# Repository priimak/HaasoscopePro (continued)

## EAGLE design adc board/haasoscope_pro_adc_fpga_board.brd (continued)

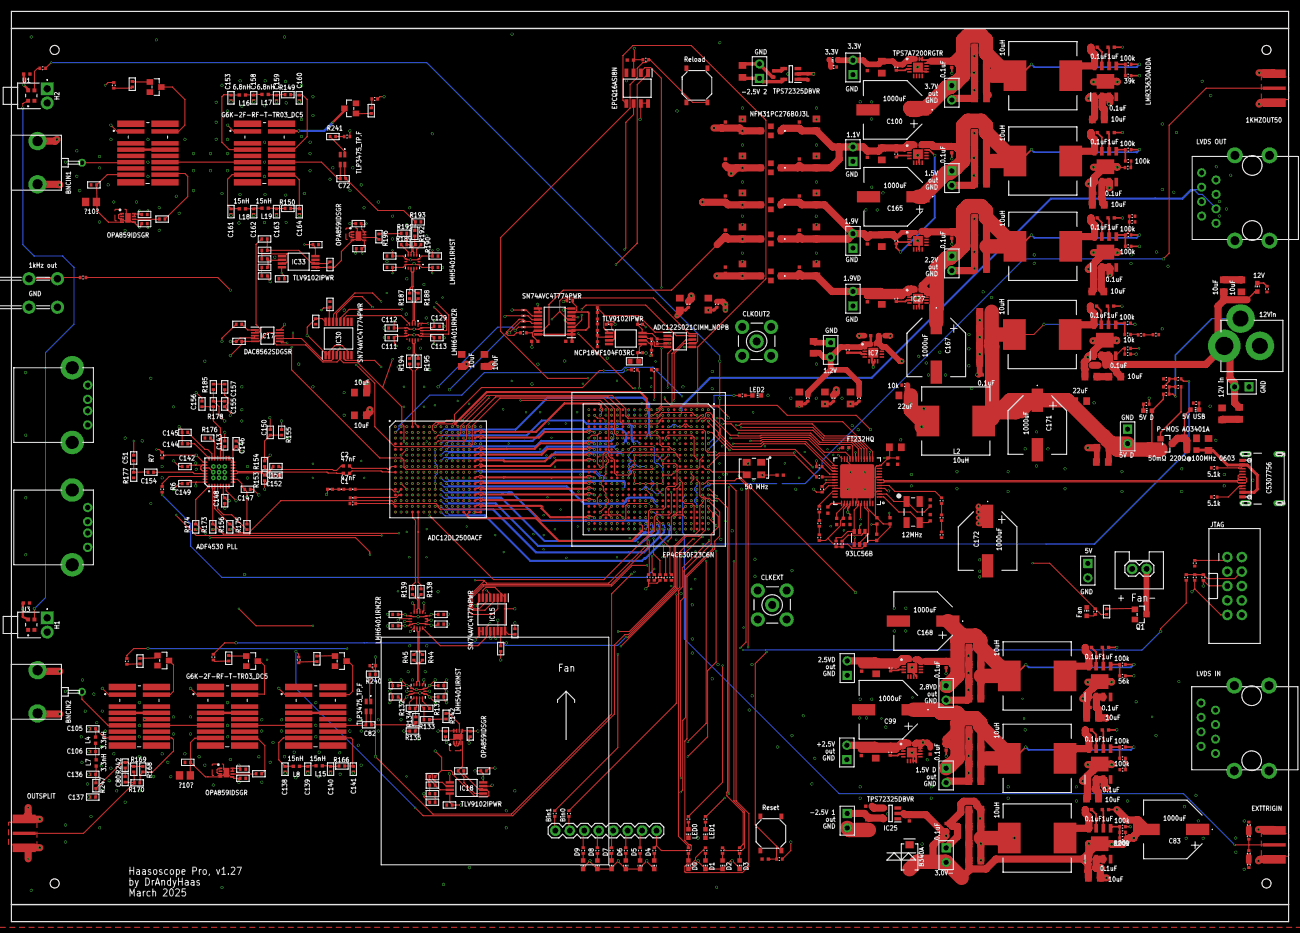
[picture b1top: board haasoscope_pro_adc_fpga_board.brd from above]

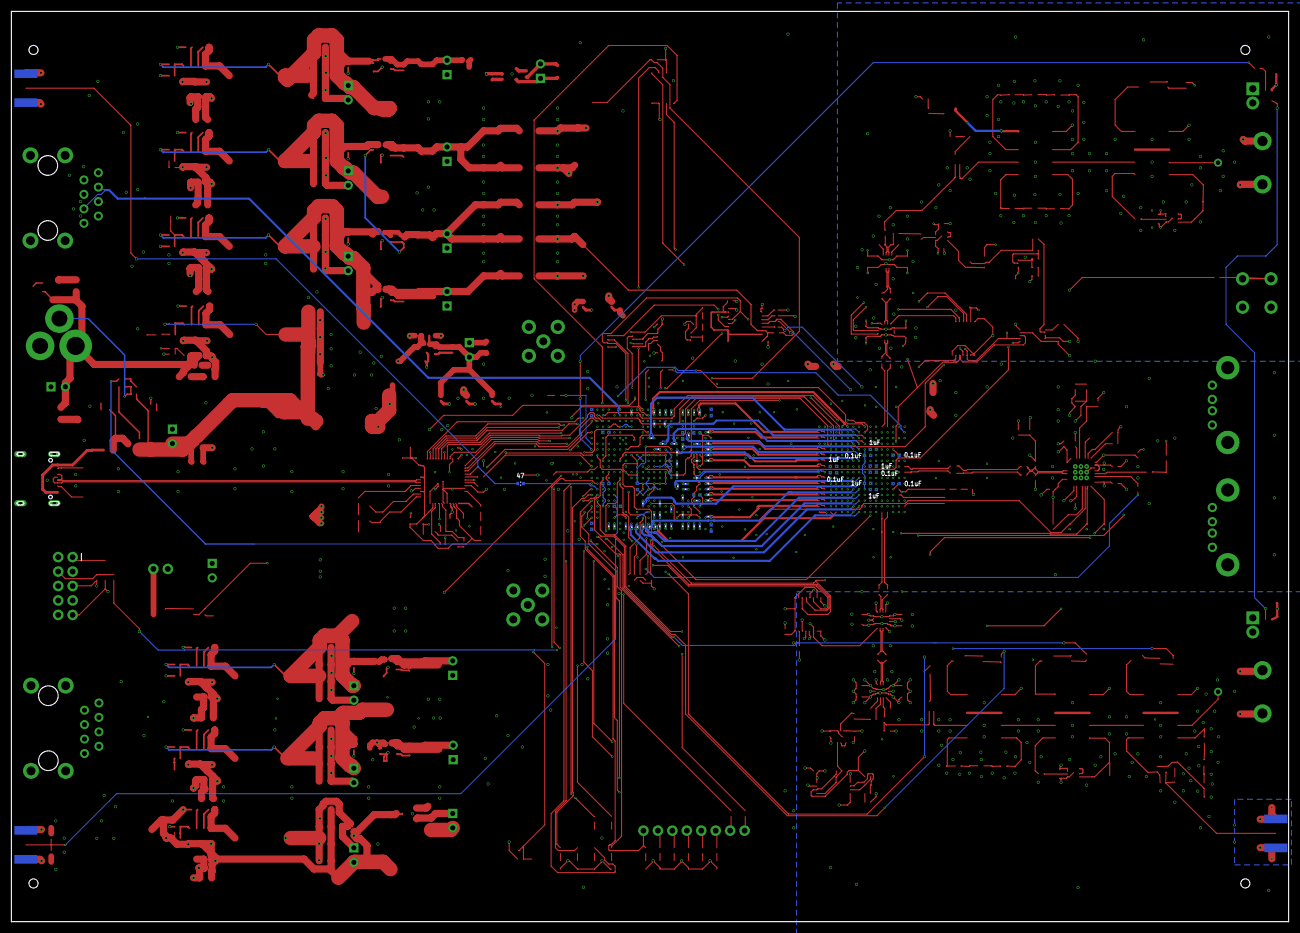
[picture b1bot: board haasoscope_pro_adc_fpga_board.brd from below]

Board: 10 copper layers, 224.5 x 160.0 mm, 632 parts (82 on the bottom side), 494 nets.

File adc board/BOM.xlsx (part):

0 | 0402_RES | R128,R129 | C17168 0402WGF0000TCE 62.5mW Thick Film Resistors 50V ±800ppm/℃ ±1% 0Ω 0402 Chi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
0 | RES-0402 | R15,R18,R81,R87,R88,R89,R90 | C17168 0402WGF0000TCE 62.5mW Thick Film Resistors 50V ±800ppm/℃ ±1% 0Ω 0402 Chi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
0 | R0402 | R142,R149,R150,R155,R166,R196,R245,R247 | C17168 0402WGF0000TCE 62.5mW Thick Film Resistors 50V ±800ppm/℃ ±1% 0Ω 0402 Chi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
22.6 | R0402 | R134,R192 | C172030 WR04X22R6FTL 62.5mW Thick Film Resistors 50V ±100ppm/℃ ±1% 22.6Ω 0402 C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
39 | R0402 | R44,R45,R138,R139 | C185420 RC0402FR-0739RL 62.5mW Thick Film Resistors 50V ±100ppm/℃ ±1% 39Ω 0402 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
39 | RES-0402 | R184 | C185420 RC0402FR-0739RL 62.5mW Thick Film Resistors 50V ±100ppm/℃ ±1% 39Ω 0402 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
39 | R0402 | R187,R188,R194,R195 | C185420 RC0402FR-0739RL 62.5mW Thick Film Resistors 50V ±100ppm/℃ ±1% 39Ω 0402 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
47 | R0402 | R43 | C25118 0402WGF470JTCE 62.5mW Thick Film Resistors 50V ±1% ±200ppm/℃ 47Ω 0402 Ch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
47 | RES-0402 | R31 | C25118 0402WGF470JTCE 62.5mW Thick Film Resistors 50V ±1% ±200ppm/℃ 47Ω 0402 Ch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
47 | R0402 | R242 | C25118 0402WGF470JTCE 62.5mW Thick Film Resistors 50V ±1% ±200ppm/℃ 47Ω 0402 Ch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
47 | RES-0402 | R160 | C25118 0402WGF470JTCE 62.5mW Thick Film Resistors 50V ±1% ±200ppm/℃ 47Ω 0402 Ch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
47 | RES-0402 | R211 | C25118 0402WGF470JTCE 62.5mW Thick Film Resistors 50V ±1% ±200ppm/℃ 47Ω 0402 Ch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
47 | R0402 | R153,R154,R159 | C25118 0402WGF470JTCE 62.5mW Thick Film Resistors 50V ±1% ±200ppm/℃ 47Ω 0402 Ch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
47 | RES-0402 | R136 | C25118 0402WGF470JTCE 62.5mW Thick Film Resistors 50V ±1% ±200ppm/℃ 47Ω 0402 Ch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
47 | RES-0402 | R210 | C25118 0402WGF470JTCE 62.5mW Thick Film Resistors 50V ±1% ±200ppm/℃ 47Ω 0402 Ch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
47 | R0402 | R168,R169,R170,R177 | C25118 0402WGF470JTCE 62.5mW Thick Film Resistors 50V ±1% ±200ppm/℃ 47Ω 0402 Ch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
66.5 | R0402 | R133,R191 | C368442 WR04X66R5FTL 62.5mW Thick Film Resistors 50V ±100ppm/℃ ±1% 66.5Ω 0402 C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
100 | R0201 | R1,R2,R3,R4 | C270366 0201WMF1000TEE 50mW Thick Film Resistors 25V ±1% ±200ppm/℃ 100Ω 0201 Ch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
100 | R0201 | R17,R19,R20,R21,R23,R24,R25,R26,R39,R54,R55,R56,R57,R58,R59,R60,R61,R62,R63,R64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 | C270366 0201WMF1000TEE 50mW Thick Film Resistors 25V ±1% ±200ppm/℃ 100Ω 0201 Ch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
120 | R0402 | R240,R241 | C25079 0402WGF1200TCE 62.5mW Thick Film Resistors 50V ±100ppm/℃ ±1% 120Ω 0402 C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
127 | R0402 | R131,R132,R189,R190 | C1509602 ARG02BTC1270 62.5mW Thin Film Resistor 50V ±25ppm/℃ ±0.1% 127Ω 0402 Ch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
220 | R0402 | R135,R193 | C25091 0402WGF2200TCE 62.5mW Thick Film Resistors 50V ±100ppm/℃ ±1% 220Ω 0402 C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
357 | RES-0402 | R50 | C423184 0402WGF3570TCE 62.5mW Thick Film Resistors 50V ±100ppm/℃ ±1% 357Ω 0402 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
357 | R0402 | R185 | C423184 0402WGF3570TCE 62.5mW Thick Film Resistors 50V ±100ppm/℃ ±1% 357Ω 0402 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
0.1uF | C0402 | C78,C84,C85,C86,C87,C88,C89,C90,C91,C92,C93,C94,C95,C96,C97,C98,C107,C108,C109,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 | C1525 CL05B104KO5NNNC 16V 100nF X7R ±10% 0402 Multilayer Ceramic Capacitors MLC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
0.1uF | RESC0402_N | C3,C4,C7,C9,C17,C19,C27,C29,C37,C39 | C1525 CL05B104KO5NNNC 16V 100nF X7R ±10% 0402 Multilayer Ceramic Capacitors MLC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
0.1uF | RESC0402_N | C12,C20,C23,C31,C33,C61,C62,C63,C64,C65,C66,C67,C68,C69,C70,C71 | C1525 CL05B104KO5NNNC 16V 100nF X7R ±10% 0402 Multilayer Ceramic Capacitors MLC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
0.1uF | RESC0402_N | C58,C59,C60,C73,C74 | C1525 CL05B104KO5NNNC 16V 100nF X7R ±10% 0402 Multilayer Ceramic Capacitors MLC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
0.1uF | C0402 | C129,C130,C131,C132,C133,C134,C135,C142,C143,C144,C145,C146,C147,C148,C149,C150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 | C1525 CL05B104KO5NNNC 16V 100nF X7R ±10% 0402 Multilayer Ceramic Capacitors MLC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
0.1uF | C0402 | C75 | C1525 CL05B104KO5NNNC 16V 100nF X7R ±10% 0402 Multilayer Ceramic Capacitors MLC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
0.1uF | RESC0402_N | C53,C54 | C1525 CL05B104KO5NNNC 16V 100nF X7R ±10% 0402 Multilayer Ceramic Capacitors MLC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
0.1uF | RESC0402_N | C114,C115,C116,C117,C119,C121,C122,C123,C124,C125 | C1525 CL05B104KO5NNNC 16V 100nF X7R ±10% 0402 Multilayer Ceramic Capacitors MLC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
0.1uF | 0402_CAP | C50 | C1525 CL05B104KO5NNNC 16V 100nF X7R ±10% 0402 Multilayer Ceramic Capacitors MLC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
0.1uF | 0402_CAP | C44 | C1525 CL05B104KO5NNNC 16V 100nF X7R ±10% 0402 Multilayer Ceramic Capacitors MLC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
0.1uF | RESC0402_N | C47,C49 | C1525 CL05B104KO5NNNC 16V 100nF X7R ±10% 0402 Multilayer Ceramic Capacitors MLC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
0.1uF | C0402 | C55,C56 | C1525 CL05B104KO5NNNC 16V 100nF X7R ±10% 0402 Multilayer Ceramic Capacitors MLC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
0.1uF | RESC0402_N | C77 | C1525 CL05B104KO5NNNC 16V 100nF X7R ±10% 0402 Multilayer Ceramic Capacitors MLC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
0.1uF | C0402 | C51 | C1525 CL05B104KO5NNNC 16V 100nF X7R ±10% 0402 Multilayer Ceramic Capacitors MLC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
0.1uF | RESC0402_N | C245,C247,C249,C250,C252,C254,C256,C258,C259,C260,C262,C263,C264,C266,C267,C268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 | C307331 CL05B104KB54PNC 50V 100nF X7R ±10% 0402 Multilayer Ceramic Capacitors M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
1.0pF | C0402 | C101,C103,C105,C136 | C1550 0402CG1R0C500NT 50V 1pF C0G 0402 Multilayer Ceramic Capacitors MLCC - SMD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
1.5pF | C0402 | C102,C106 | C1552 0402CG1R5C500NT 50V 1.5pF C0G 0402 Multilayer Ceramic Capacitors MLCC - S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
100k | RES-0402 | R137,R163,R209,R221,R223,R224,R225,R226,R227,R229,R230,R231,R232,R233 | C25741 0402WGF1003TCE 62.5mW Thick Film Resistors 50V ±100ppm/℃ ±1% 100kΩ 0402 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
10k | 0402_RES | R186,R198 | C25744 0402WGF1002TCE 62.5mW Thick Film Resistors 50V ±100ppm/℃ ±1% 10kΩ 0402 C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
10k | RES-0402 | R151 | C25744 0402WGF1002TCE 62.5mW Thick Film Resistors 50V ±100ppm/℃ ±1% 10kΩ 0402 C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
10k | R0402 | R173,R174,R175 | C25744 0402WGF1002TCE 62.5mW Thick Film Resistors 50V ±100ppm/℃ ±1% 10kΩ 0402 C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
10k | 0402_RES | R125,R127,R130 | C25744 0402WGF1002TCE 62.5mW Thick Film Resistors 50V ±100ppm/℃ ±1% 10kΩ 0402 C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
10k | RES-0402 | R212,R213,R214,R215,R216,R219,R220,R234,R237,R239 | C25744 0402WGF1002TCE 62.5mW Thick Film Resistors 50V ±100ppm/℃ ±1% 10kΩ 0402 C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
10k | RES-0402 | R161 | C25744 0402WGF1002TCE 62.5mW Thick Film Resistors 50V ±100ppm/℃ ±1% 10kΩ 0402 C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
10k | R0402 | R156 | C25744 0402WGF1002TCE 62.5mW Thick Film Resistors 50V ±100ppm/℃ ±1% 10kΩ 0402 C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
10k | RES-0402 | R5,R27,R38,R78,R79,R80,R82,R83,R84,R85,R86,R91,R92,R121,R123 | C25744 0402WGF1002TCE 62.5mW Thick Film Resistors 50V ±100ppm/℃ ±1% 10kΩ 0402 C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
10uF | RESC0805_N | C6,C8,C10,C13,C16,C18,C21,C24,C26,C28,C34,C36,C38,C40,C41,C42,C43,C46,C48,C52,C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 | C15850 CL21A106KAYNNNE 25V 10uF X5R ±10% 0805 Multilayer Ceramic Capacitors MLC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
10uH | CDRH125 | L1,L9,L10,L11,L12,L13,L14 | C339970 YDRH105R-100M 4.45A 10uH ±20% SMD,10.1x10.1mm Power Inductors ROHS Exte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
11pF | C0402 | C139,C162 | C161525 GRM1555C1H110JA01D 50V 11pF C0G ±5% 0402 Multilayer Ceramic Capacitors 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
12MHz | CRYSTAL-SMD-5X3 | Y3 | C2901628 SX5B12.000F1620F30 12MHz SMD crystal oscillator 16pF ±20ppm ±30ppm SMD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
15nH | RESC0402_N | L8,L15,L18,L19 | C27143 SDCL1005C15NJTDF 300mA 15nH ±5% 500mΩ 0402 Inductors (SMD) ROHS Extended
16pF | RESC0402_N | C127,C128 | C77590 CC0402JRNPO9BN160 50V 16pF NP0 ±5% 0402 Multilayer Ceramic Capacitors ML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
16pF | C0402 | C80 | C77590 CC0402JRNPO9BN160 50V 16pF NP0 ±5% 0402 Multilayer Ceramic Capacitors ML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
1k | RES-0402 | R179 | C11702 0402WGF1001TCE 62.5mW Thick Film Resistors 50V ±100ppm/℃ ±1% 1kΩ 0402 Ch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
1k | R0402 | R180,R181,R197,R199,R200,R201 | C11702 0402WGF1001TCE 62.5mW Thick Film Resistors 50V ±100ppm/℃ ±1% 1kΩ 0402 Ch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
1k | RES-0402 | R236,R238,R243,R244 | C11702 0402WGF1001TCE 62.5mW Thick Film Resistors 50V ±100ppm/℃ ±1% 1kΩ 0402 Ch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
1k | 0402_RES | R122,R124,R126 | C11702 0402WGF1001TCE 62.5mW Thick Film Resistors 50V ±100ppm/℃ ±1% 1kΩ 0402 Ch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
1k | 0402_RES | R202,R203 | C11702 0402WGF1001TCE 62.5mW Thick Film Resistors 50V ±100ppm/℃ ±1% 1kΩ 0402 Ch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
1k | R0402 | R162,R164,R171,R172,R178 | C11702 0402WGF1001TCE 62.5mW Thick Film Resistors 50V ±100ppm/℃ ±1% 1kΩ 0402 Ch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
1k | RES-0402 | R206 | C11702 0402WGF1001TCE 62.5mW Thick Film Resistors 50V ±100ppm/℃ ±1% 1kΩ 0402 Ch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
1k | R0402 | R208 | C11702 0402WGF1001TCE 62.5mW Thick Film Resistors 50V ±100ppm/℃ ±1% 1kΩ 0402 Ch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
1k | R0402 | R140,R141,R143,R144,R145,R146,R147 | C11702 0402WGF1001TCE 62.5mW Thick Film Resistors 50V ±100ppm/℃ ±1% 1kΩ 0402 Ch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

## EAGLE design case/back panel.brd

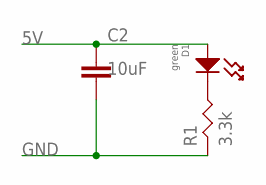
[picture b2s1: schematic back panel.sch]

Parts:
C2: 10uF; RESC0805_N
D1: green; LED0805
R1: 3.3k; RES-0402

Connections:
5V: C2.1, D1.ANODE
GND: C2.2, R1.P$1
unnamed: D1.CATHODE, R1.P$2

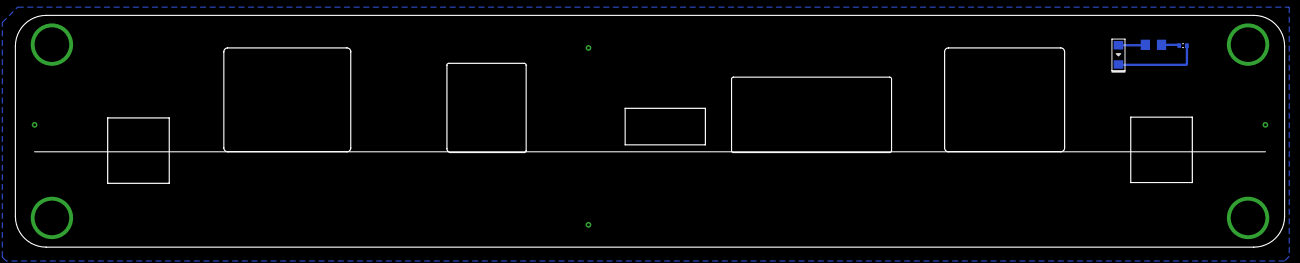
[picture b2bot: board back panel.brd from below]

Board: 2 copper layers, 165.0 x 30.1 mm, 5 parts (3 on the bottom side), 3 nets.

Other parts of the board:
U$1: CE_5MM
U$2: FCC_6.1X16MM

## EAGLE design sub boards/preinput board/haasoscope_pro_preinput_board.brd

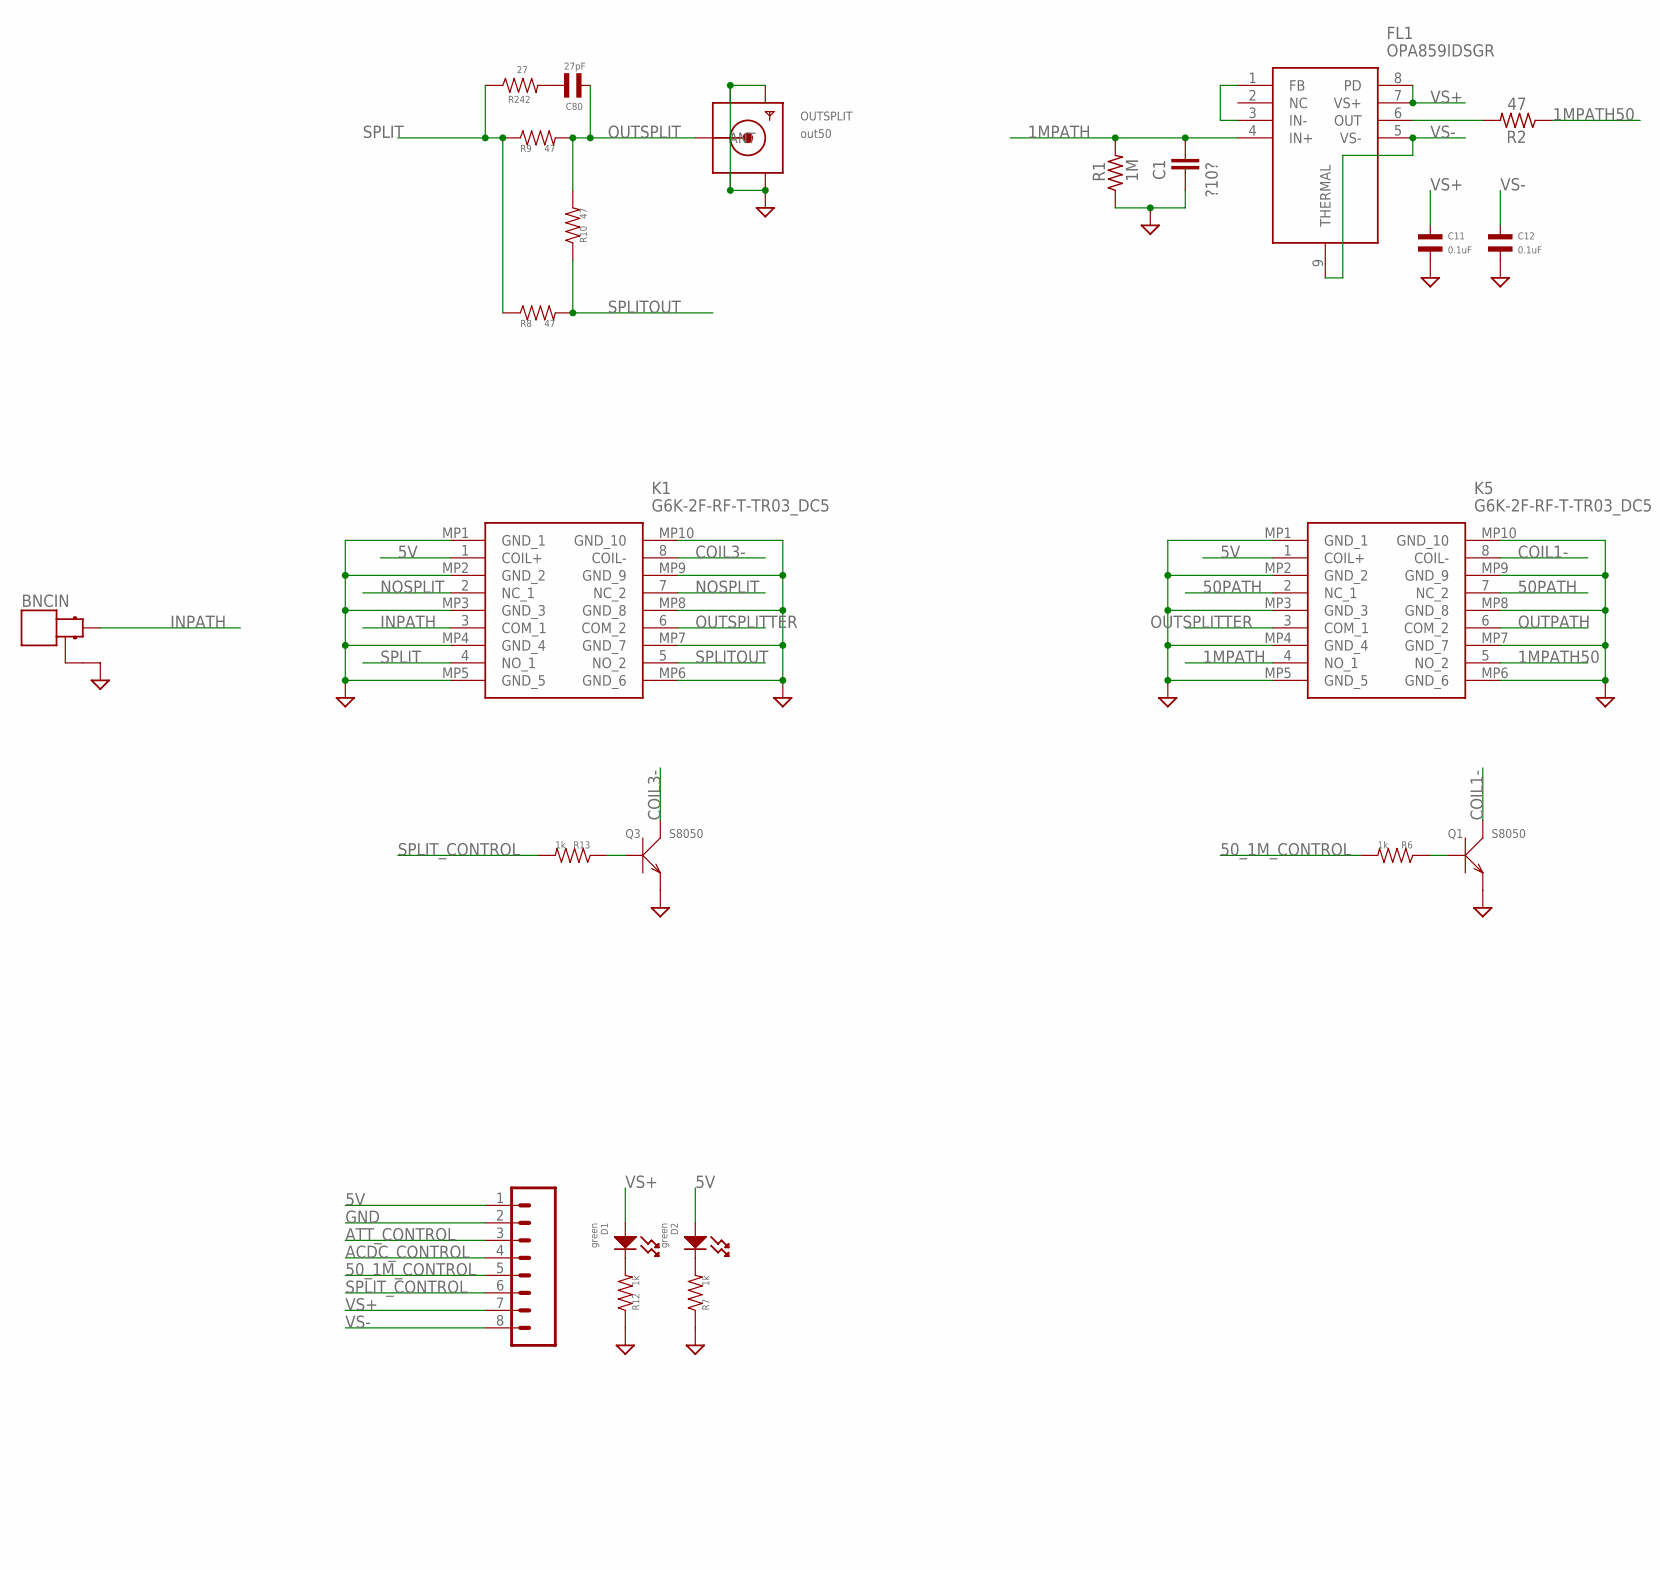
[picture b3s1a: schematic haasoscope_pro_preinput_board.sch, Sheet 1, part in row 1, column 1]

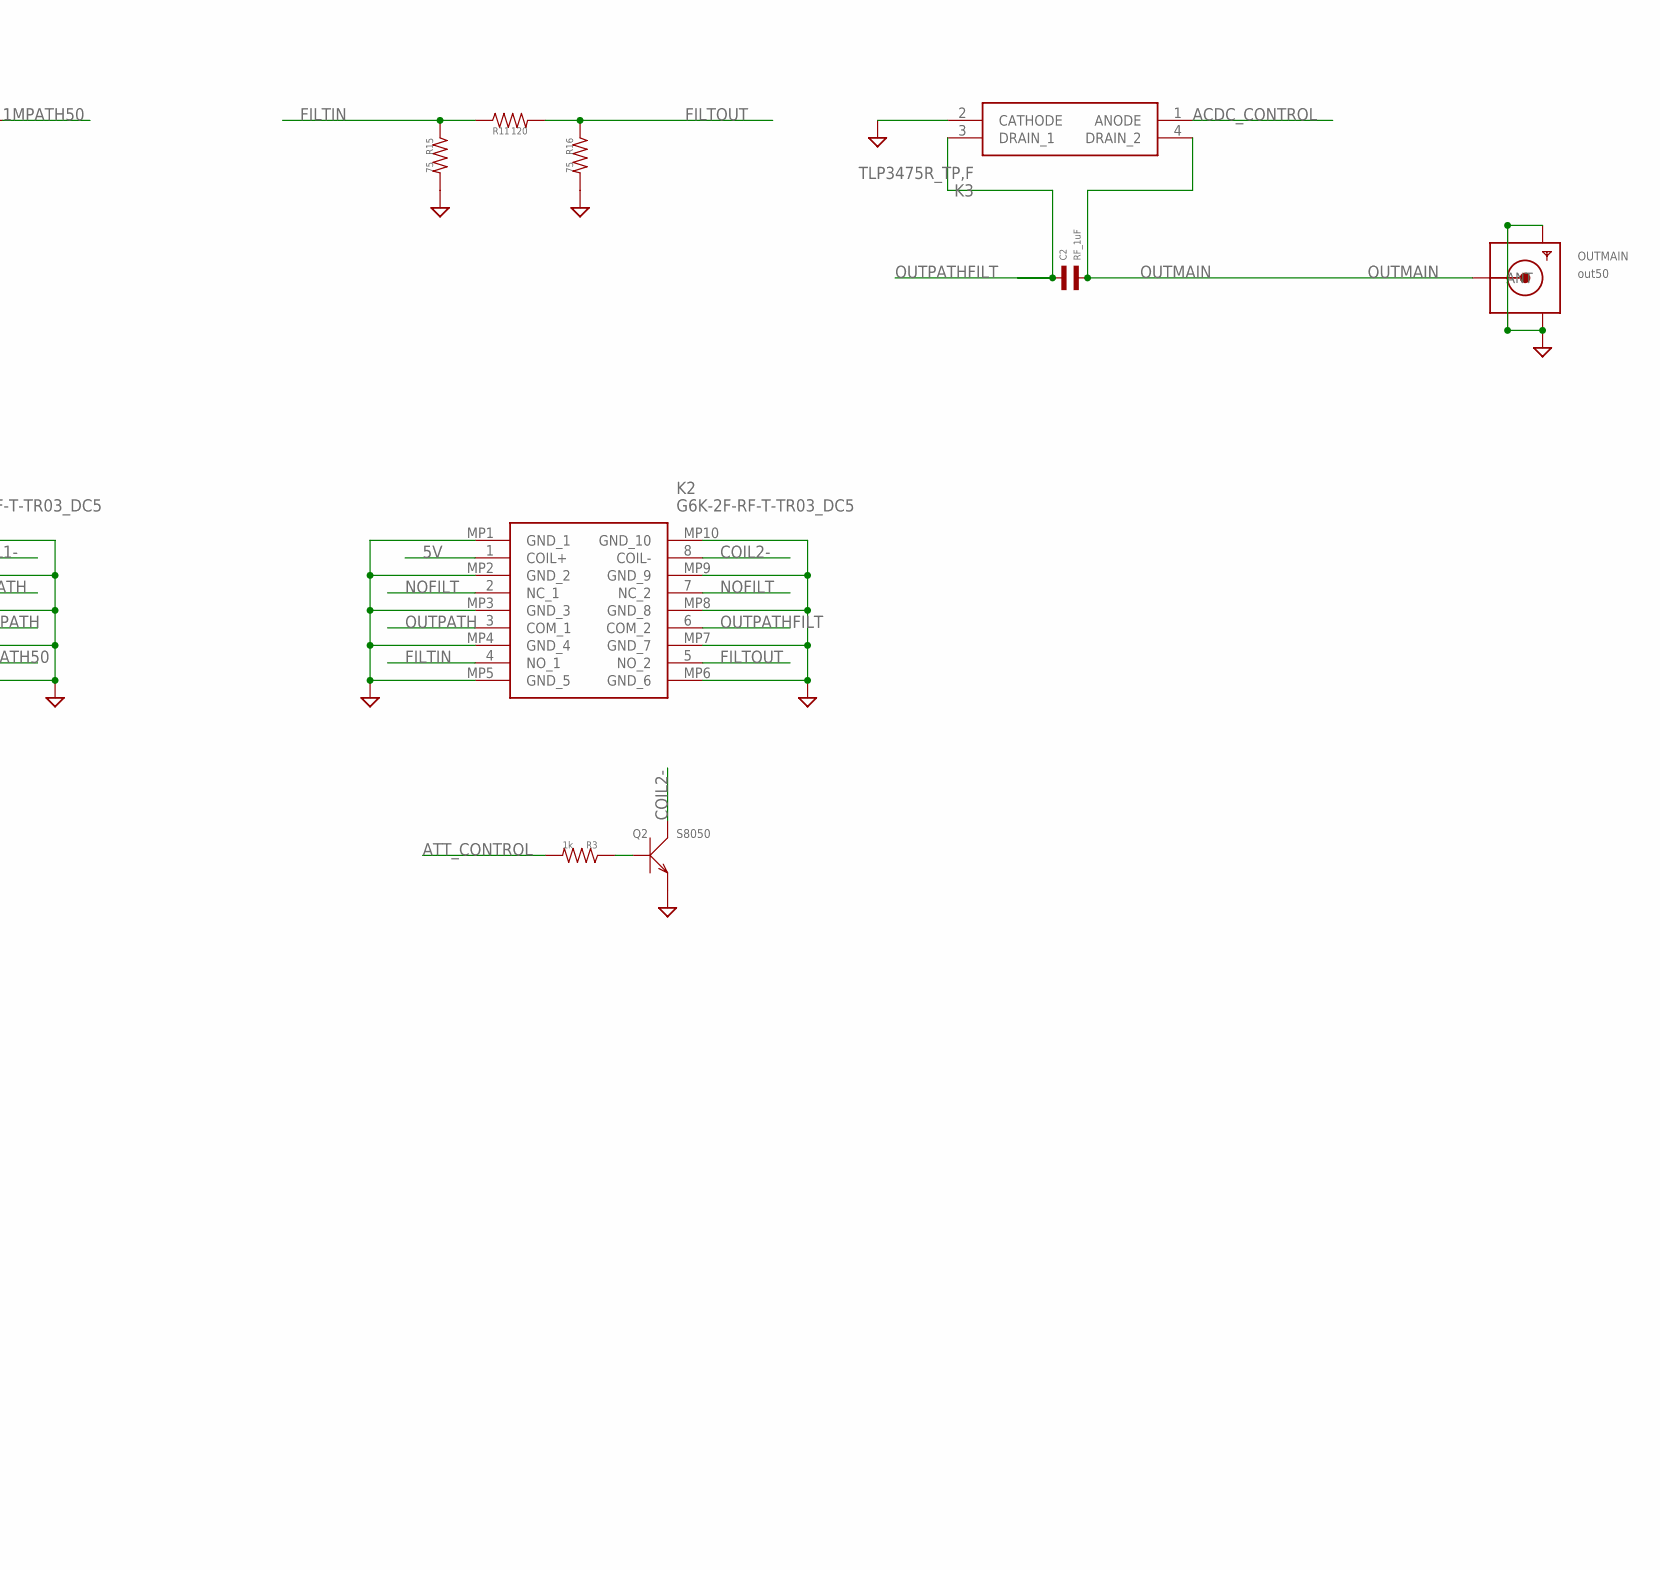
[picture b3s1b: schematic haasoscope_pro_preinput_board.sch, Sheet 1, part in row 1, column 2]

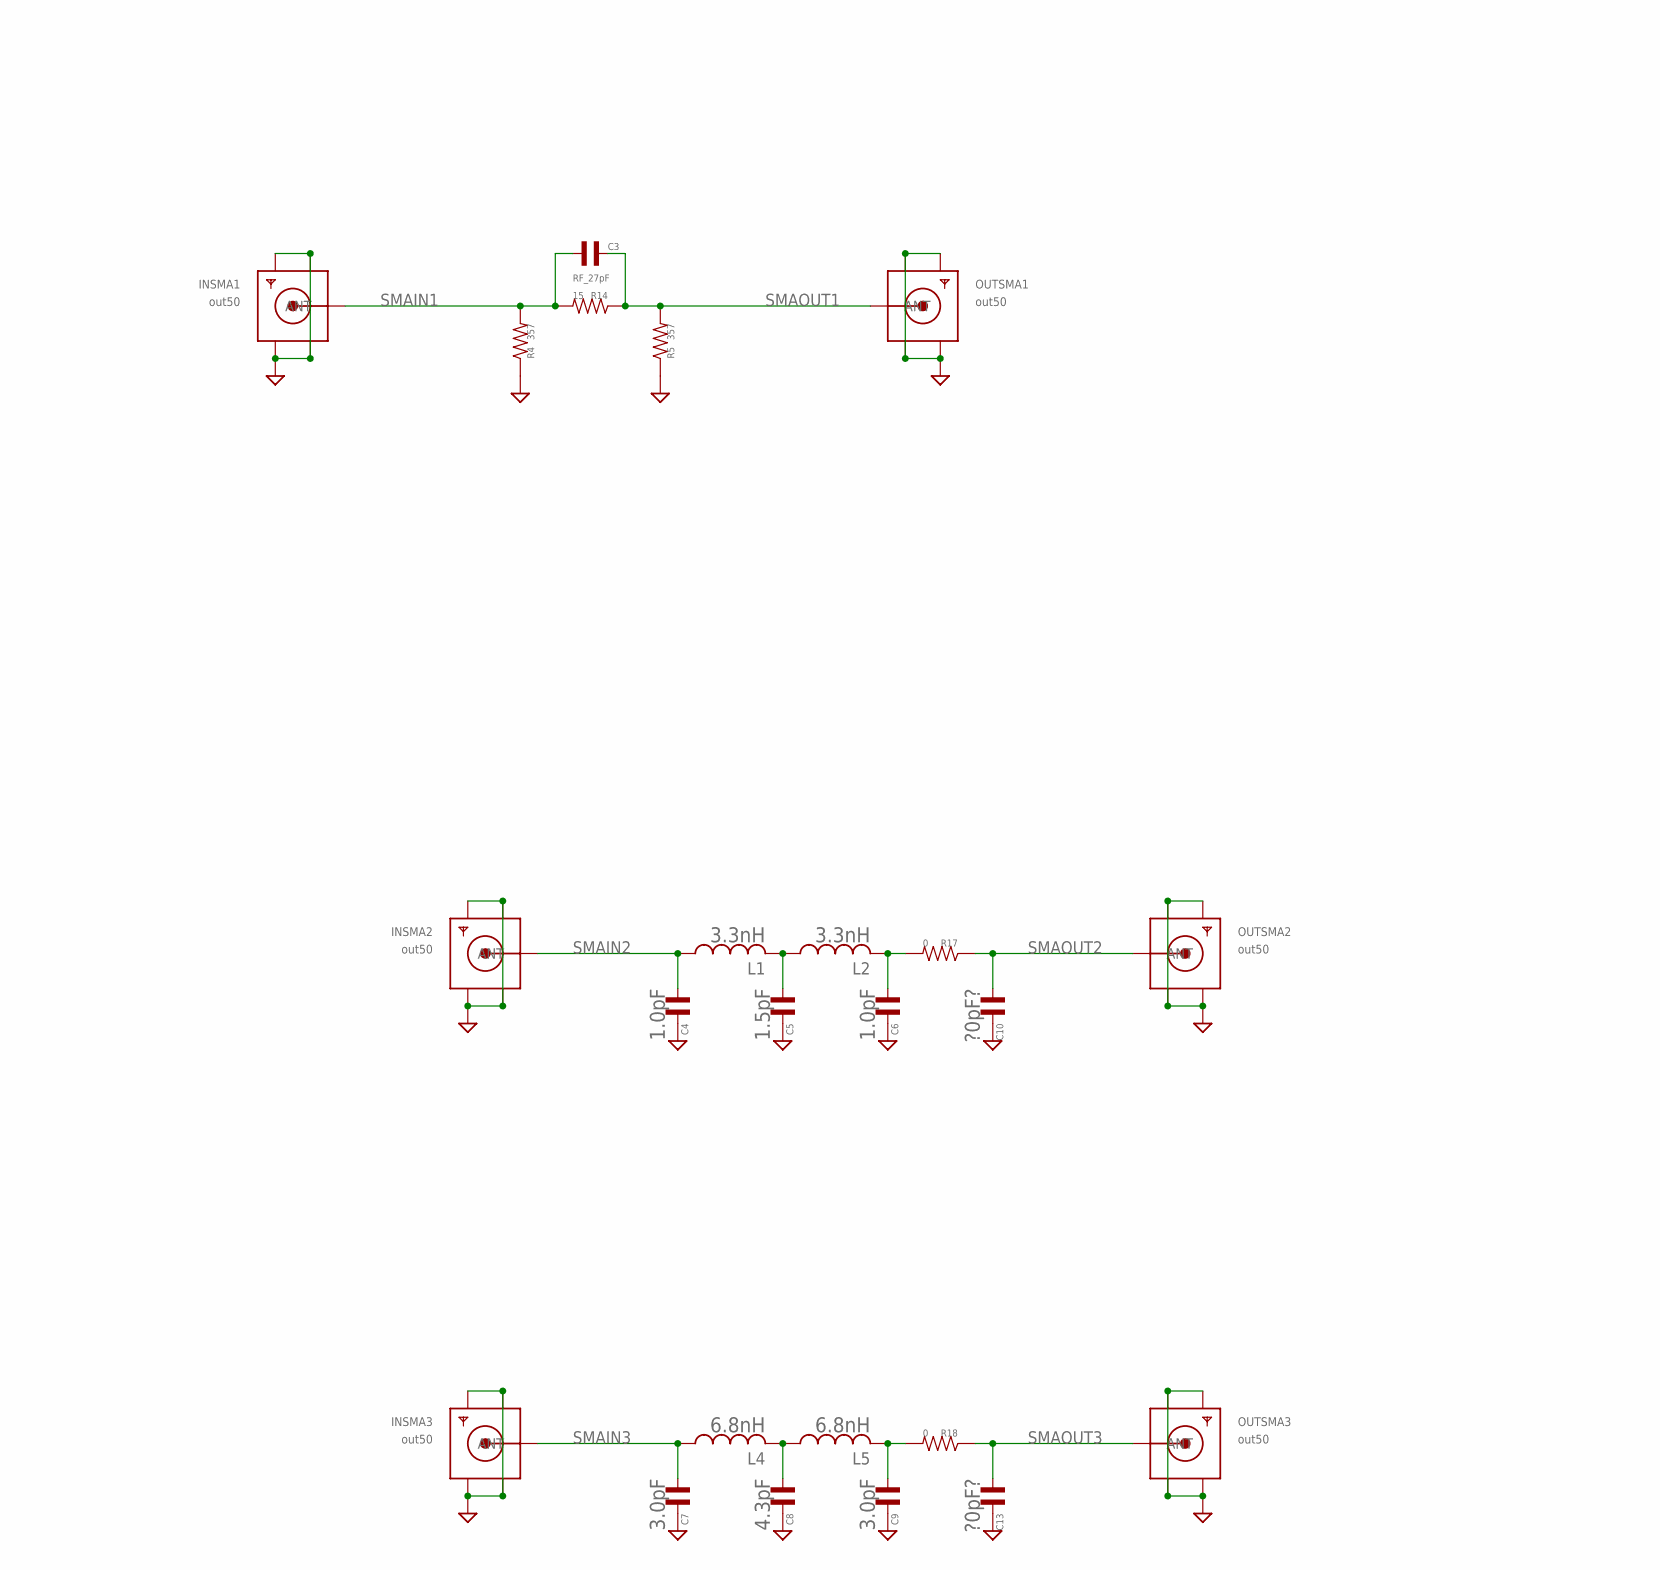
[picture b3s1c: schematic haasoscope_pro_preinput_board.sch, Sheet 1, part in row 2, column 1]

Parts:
BNCIN: MOLEX_BNC_73100-0105; MOLEX-BNC-73100-0105; MPN 73100-0105
C1: ?10?; C0805
C2: RF_1uF; C0402; LCSC C52923
C3: RF_27pF; C0402; LCSC C52923
C4, C6: 1.0pF; C0402; LCSC C52923
C5: 1.5pF; C0402; LCSC C52923
C7, C9: 3.0pF; C0402; LCSC C52923
C8: 4.3pF; C0402; LCSC C52923
C10, C13: ?0pF?; C0402; LCSC C52923
C11, C12: 0.1uF; C0402
C80: 27pF; C0402; LCSC C52923
D1, D2: green; LED0603; LCSC C2286
FL1: OPA859IDSGR; SON50P200X200X80-9N
INSMA1, INSMA2, INSMA3: out50; SMA_EDGELAUNCH
J4: 8pin; 1X08
K1, K2, K5: G6K-2F-RF-T-TR03_DC5; G6K2FRFTTR03DC5
K3: TLP3475R_TP,F; TLP3475RTPF; MANUFACTURER_PART_NUMBER TLP3475R(TP,F
L1, L2: 3.3nH; RESC0402_N
L4, L5: 6.8nH; RESC0402_N
OUTMAIN: out50; SMA_EDGELAUNCH
OUTSMA1, OUTSMA2, OUTSMA3: out50; SMA_EDGELAUNCH
OUTSPLIT: out50; SMA_EDGELAUNCH
Q1, Q2, Q3: S8050; SOT-23; LCSC C7420370
R1: 1M; R0805
R2: 47; R0805
R3, R6, R7, R12, R13: 1k; R0402
R4, R5: 357; R0402
R8, R9, R10: 47; R0402
R11: 120; R0402
R14: 15; R0402
R15, R16: 75; R0402
R17, R18: 0; R0402
R242: 27; R0402

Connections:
1MPATH: C1.2, FL1.4 (IN+), K5.4 (NO_1), R1.2
1MPATH50: K5.5 (NO_2), R2.1
5V: D2.ANODE, J4.1, K1.1 (COIL+), K2.1 (COIL+), K5.1 (COIL+)
50PATH: K5.2 (NC_1), K5.7 (NC_2)
50_1M_CONTROL: J4.5, R6.P$2
ACDC_CONTROL: J4.4, K3.1 (ANODE)
ATT_CONTROL: J4.3, R3.P$2
COIL1-: K5.8 (COIL-), Q1.3 (C)
COIL2-: K2.8 (COIL-), Q2.3 (C)
COIL3-: K1.8 (COIL-), Q3.3 (C)
FILTIN: K2.4 (NO_1), R11.P$1, R15.P$1
FILTOUT: K2.5 (NO_2), R11.P$2, R16.P$1
GND: BNCIN.GND1 (GND), BNCIN.GND2 (GND), C1.1, C4.P$2, C5.P$2, C6.P$2, C7.P$2, C8.P$2, C9.P$2, C10.P$2, C11.P$2, C12.P$2, C13.P$2, INSMA1.GND@1 (GND4), INSMA1.GND@2 (GND3), INSMA1.GND@3 (GND2), INSMA1.GND@4 (GND1), INSMA2.GND@1 (GND4), INSMA2.GND@2 (GND3), INSMA2.GND@3 (GND2), INSMA2.GND@4 (GND1), INSMA3.GND@1 (GND4), INSMA3.GND@2 (GND3), INSMA3.GND@3 (GND2), INSMA3.GND@4 (GND1), J4.2, K1.MP1 (GND_1), K1.MP2 (GND_2), K1.MP3 (GND_3), K1.MP4 (GND_4), K1.MP5 (GND_5), K1.MP6 (GND_6), K1.MP7 (GND_7), K1.MP8 (GND_8), K1.MP9 (GND_9), K1.MP10 (GND_10), K2.MP1 (GND_1), K2.MP2 (GND_2), K2.MP3 (GND_3), K2.MP4 (GND_4), K2.MP5 (GND_5), K2.MP6 (GND_6), K2.MP7 (GND_7), K2.MP8 (GND_8), K2.MP9 (GND_9), K2.MP10 (GND_10), K3.2 (CATHODE), K5.MP1 (GND_1), K5.MP2 (GND_2), K5.MP3 (GND_3), K5.MP4 (GND_4), K5.MP5 (GND_5), K5.MP6 (GND_6), K5.MP7 (GND_7), K5.MP8 (GND_8), K5.MP9 (GND_9), K5.MP10 (GND_10), OUTMAIN.GND@1 (GND4), OUTMAIN.GND@2 (GND3), OUTMAIN.GND@3 (GND2), OUTMAIN.GND@4 (GND1), OUTSMA1.GND@1 (GND4), OUTSMA1.GND@2 (GND3), OUTSMA1.GND@3 (GND2), OUTSMA1.GND@4 (GND1), OUTSMA2.GND@1 (GND4), OUTSMA2.GND@2 (GND3), OUTSMA2.GND@3 (GND2), OUTSMA2.GND@4 (GND1), OUTSMA3.GND@1 (GND4), OUTSMA3.GND@2 (GND3), OUTSMA3.GND@3 (GND2), OUTSMA3.GND@4 (GND1), OUTSPLIT.GND@1 (GND4), OUTSPLIT.GND@2 (GND3), OUTSPLIT.GND@3 (GND2), OUTSPLIT.GND@4 (GND1), Q1.2 (E), Q2.2 (E), Q3.2 (E), R1.1, R4.P$1, R5.P$1, R7.P$1, R12.P$1, R15.P$2, R16.P$2
INPATH: BNCIN.SIGNAL, K1.3 (COM_1)
unnamed: D1.CATHODE, R12.P$2
unnamed: Q2.1 (B), R3.P$1
unnamed: Q3.1 (B), R13.P$1
unnamed: FL1.6 (OUT), R2.2
unnamed: FL1.1 (FB), FL1.3 (IN-)
unnamed: Q1.1 (B), R6.P$1
unnamed: D2.CATHODE, R7.P$2
unnamed: C5.P$1, L1.2, L2.1
unnamed: C6.P$1, L2.2, R17.P$2
unnamed: C8.P$1, L4.2, L5.1
unnamed: C9.P$1, L5.2, R18.P$2
unnamed: C80.P$1, R242.P$2
NOFILT: K2.2 (NC_1), K2.7 (NC_2)
NOSPLIT: K1.2 (NC_1), K1.7 (NC_2)
OUTMAIN: C2.P$2, K3.4 (DRAIN_2), OUTMAIN.P (ANT)
OUTPATH: K2.3 (COM_1), K5.6 (COM_2)
OUTPATHFILT: C2.P$1, K2.6 (COM_2), K3.3 (DRAIN_1)
OUTSPLIT: C80.P$2, OUTSPLIT.P (ANT), R9.P$2, R10.P$2
OUTSPLITTER: K1.6 (COM_2), K5.3 (COM_1)
SMAIN1: C3.P$1, INSMA1.P (ANT), R4.P$2, R14.P$2
SMAIN2: C4.P$1, INSMA2.P (ANT), L1.1
SMAIN3: C7.P$1, INSMA3.P (ANT), L4.1
SMAOUT1: C3.P$2, OUTSMA1.P (ANT), R5.P$2, R14.P$1
SMAOUT2: C10.P$1, OUTSMA2.P (ANT), R17.P$1
SMAOUT3: C13.P$1, OUTSMA3.P (ANT), R18.P$1
SPLIT: K1.4 (NO_1), R8.P$1, R9.P$1, R242.P$1
SPLITOUT: K1.5 (NO_2), R8.P$2, R10.P$1
SPLIT_CONTROL: J4.6, R13.P$2
VS+: C11.P$1, D1.ANODE, FL1.7 (VS+), FL1.8 (PD), J4.7
VS-: C12.P$1, FL1.5 (VS-), FL1.9 (THERMAL), J4.8

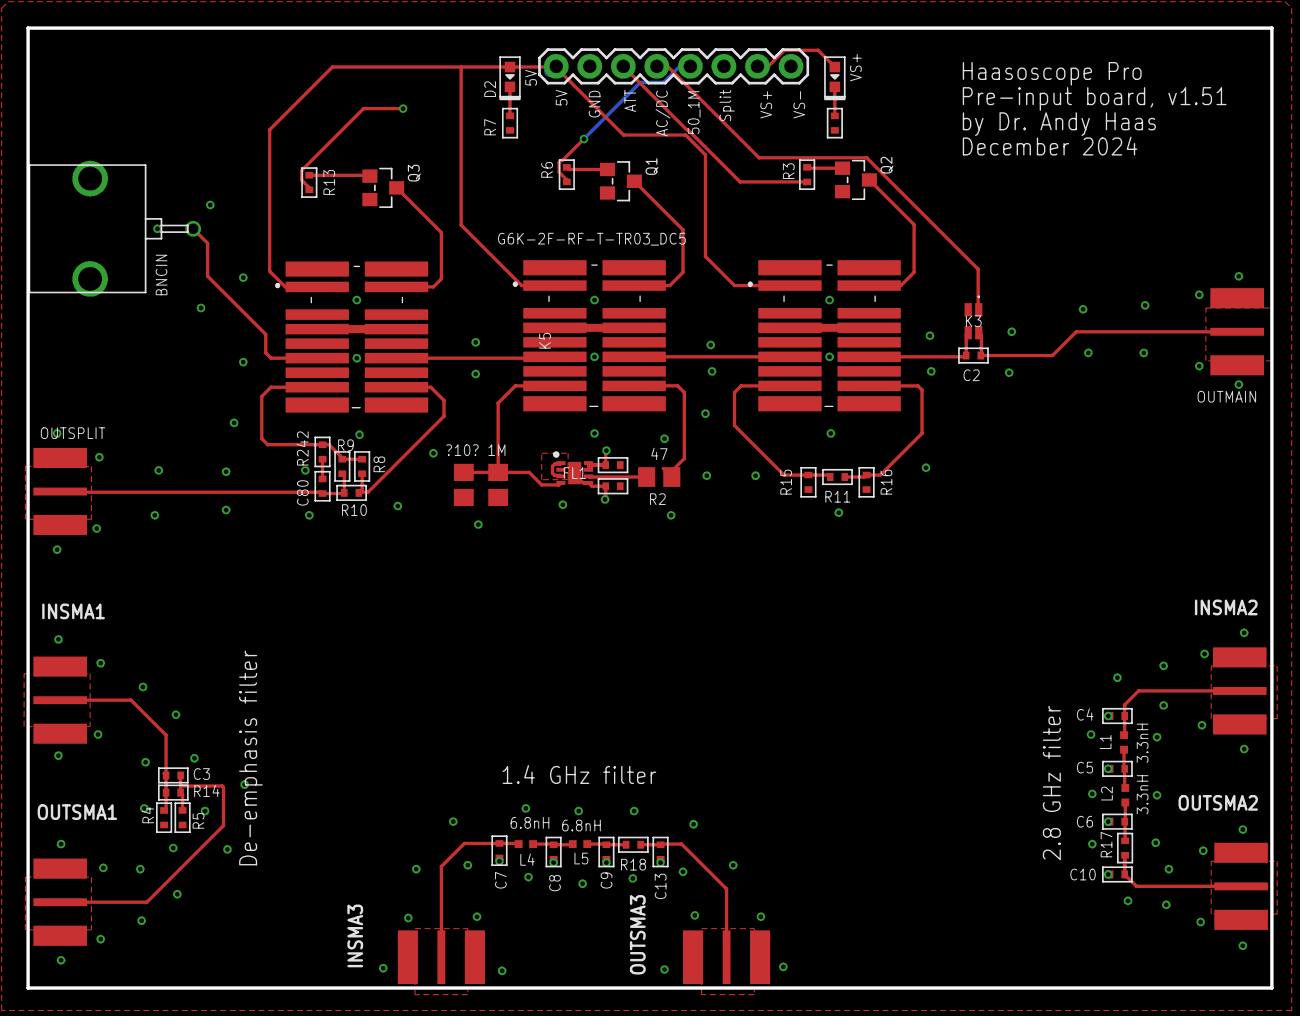
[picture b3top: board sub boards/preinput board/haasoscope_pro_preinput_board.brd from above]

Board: 4 copper layers, 94.2 x 72.7 mm, 57 parts (0 on the bottom side), 44 nets.

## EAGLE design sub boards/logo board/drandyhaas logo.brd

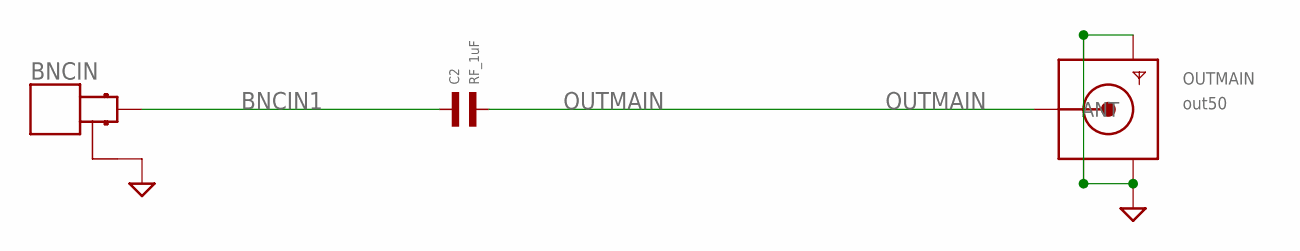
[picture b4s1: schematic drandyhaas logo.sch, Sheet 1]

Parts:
BNCIN: MOLEX_BNC_73100-0105; MOLEX-BNC-73100-0105; MPN 73100-0105
C2: RF_1uF; C0402; LCSC C52923
OUTMAIN: out50; SMA_EDGELAUNCH

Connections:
BNCIN1: BNCIN.SIGNAL, C2.P$1
GND: BNCIN.GND1 (GND), BNCIN.GND2 (GND), OUTMAIN.GND@1 (GND4), OUTMAIN.GND@2 (GND3), OUTMAIN.GND@3 (GND2), OUTMAIN.GND@4 (GND1)
OUTMAIN: C2.P$2, OUTMAIN.P (ANT)

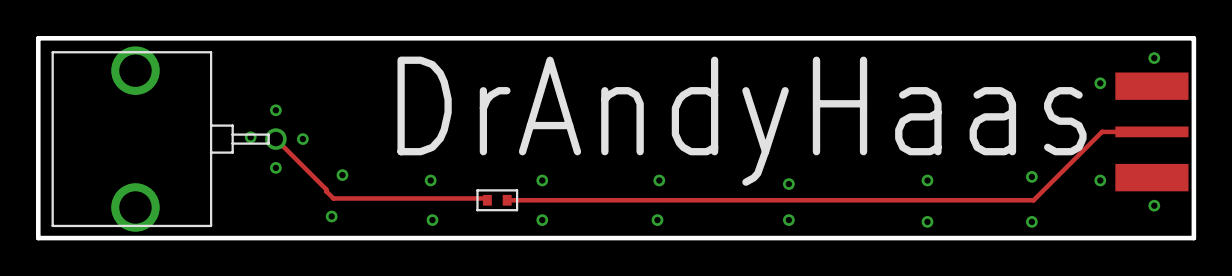
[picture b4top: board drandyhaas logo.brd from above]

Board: 4 copper layers, 64.2 x 11.1 mm, 3 parts (0 on the bottom side), 3 nets.
